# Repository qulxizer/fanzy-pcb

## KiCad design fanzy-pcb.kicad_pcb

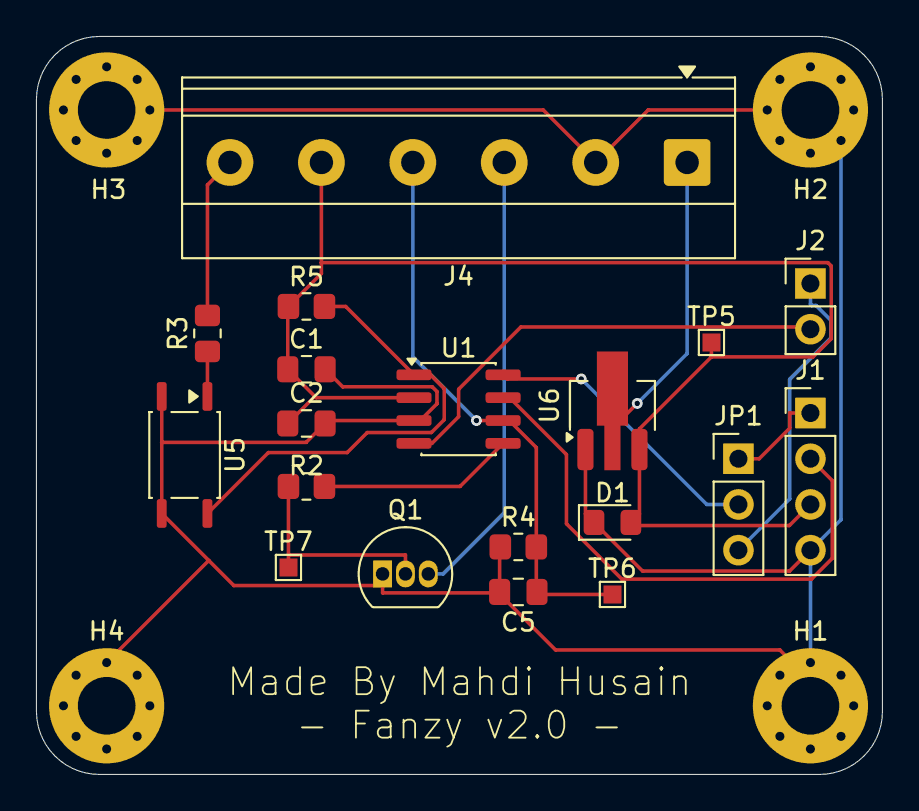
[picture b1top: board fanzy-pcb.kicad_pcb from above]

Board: 2 copper layers, 47.0 x 41.0 mm, 23 parts (0 on the bottom side), 15 nets.

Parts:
C1, C5: 100nF; C_0805_2012Metric_Pad1.18x1.45mm_HandSolder
C2: 4.7uF; C_0805_2012Metric_Pad1.18x1.45mm_HandSolder
D1: LED; LED_0805_2012Metric_Pad1.15x1.40mm_HandSolder
H1, H2, H3, H4: MountingHole_Pad; MountingHole_3.2mm_M3_Pad_Via
J1: Conn_01x04_Pin; PinHeader_1x04_P2.54mm_Vertical
J2: Conn_01x02_Pin; PinHeader_1x02_P2.54mm_Vertical
J4: Screw_Terminal_01x06; TerminalBlock_Phoenix_MKDS-1,5-6-5.08_1x06_P5.08mm_Horizont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
JP1: Jumper_3_Bridged12; PinHeader_1x03_P2.54mm_Vertical
Q1: PN2222A; TO-92_Inline
R2, R4: 1k; R_0805_2012Metric_Pad1.20x1.40mm_HandSolder
R3, R5: 10k; R_0805_2012Metric_Pad1.20x1.40mm_HandSolder
TP5, TP6, TP7: TestPoint; TestPoint_Pad_1.0x1.0mm
U1: STM32G031J6Mx; SOIC-8_3.9x4.9mm_P1.27mm
U5: TLP185
U6: HT75xx-1-SOT89; SOT-89-3_Handsoldering

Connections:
+3V3: C1.1, C2.1, D1.2 (A), J1.3, J4.5, R5.1, TP5.1, U1.2 (VDD), U6.3 (VOUT)
+12V: J4.1, U6.2 (VIN)
/AC: J4.6, R3.2
/ADC1_IN1 (PA1): C5.1, J4.4, R4.2, TP6.1, U1.6 (PA10)
/PB7/PB8/PB9/PC14: R5.2, U1.1 (PB7/PB8/PB9/PC14), U5.6
/SIG: J4.3, Q1.3 (C)
/SYS_SWCLK: J1.1, JP1.1 (A)
/SYS_SWDIO: J1.2, U1.7 (SYS_SWDIO)
/TIM1_CH1 (PA8): R2.2, U1.5 (TIM1_CH1 (PA8))
/USART2_RX (PA15): J2.1, JP1.3 (B)
/USART2_TX (PA2): J2.2, U1.4 (USART2_TX (PA2))
GND: C1.2, C2.2, C5.2, D1.1 (K), H1.1, H2.1, H3.1, H4.1, J1.4, J4.2, Q1.1 (E), R4.1, U1.3 (VSS), U5.3, U5.4, U6.1 (GND)
unnamed: JP1.2 (C), U1.8 (USART2_RX (PA15))
unnamed: Q1.2 (B), R2.1, TP7.1
unnamed: R3.1, U5.1

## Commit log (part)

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2026-05-26 Add CERN Open Hardware Licence Version 2
2026-05-26 init
2026-05-27 feat: uart port + rework
2026-06-12 rework: switching to the STM32G031J6M6 series
2026-06-18 incl: pcb
